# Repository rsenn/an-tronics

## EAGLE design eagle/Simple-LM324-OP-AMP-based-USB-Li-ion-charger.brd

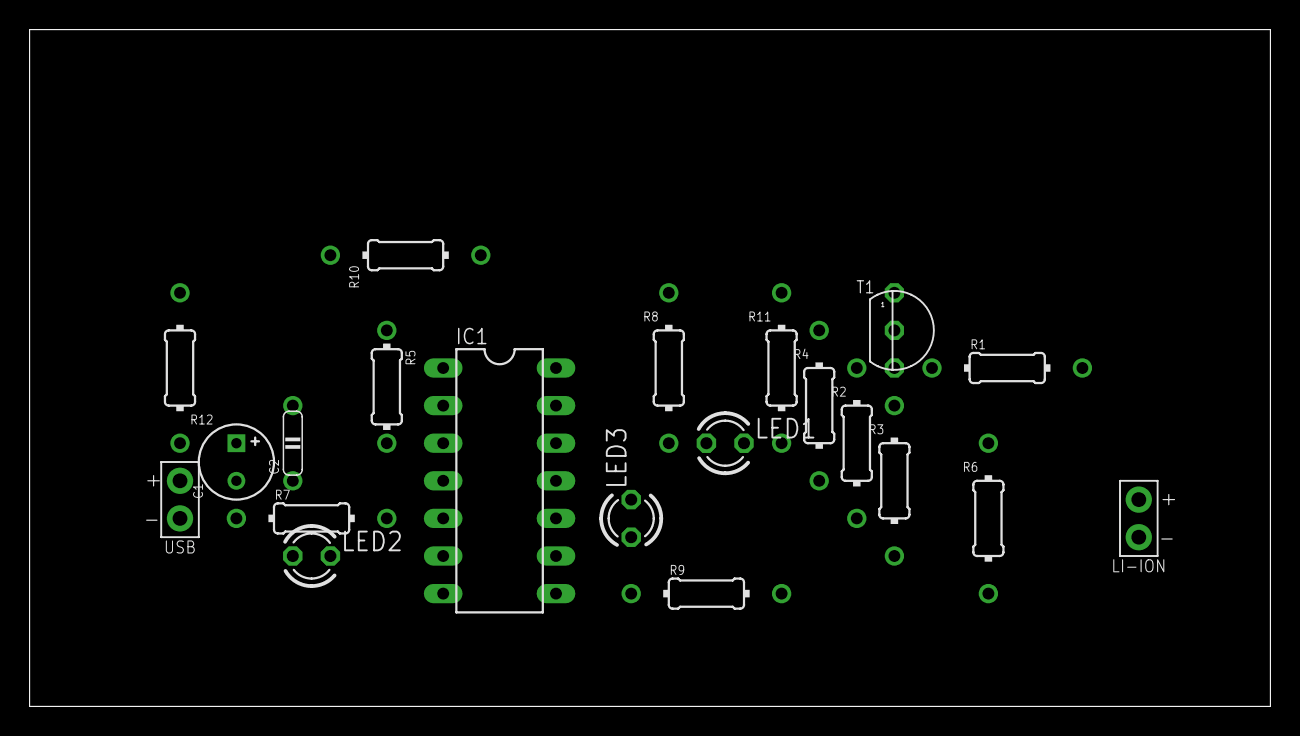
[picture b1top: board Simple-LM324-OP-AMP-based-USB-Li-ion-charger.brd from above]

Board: 2 copper layers, 83.8 x 45.7 mm, 21 parts (0 on the bottom side), 13 nets, no tracks yet.

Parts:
C1: 100uF/16V; E2,5-5
C2: 68nF; C050-020X044
IC1: LM324N; DIL14
LED1: Red; LED3MM
LED2: Green; LED3MM
LED3: Blue; LED3MM
LI-ION: SPAD+-+-; SPAD+-
R1: 1; 0204/10
R2: 2.7k; 0204/10-V
R3: 2.2k; 0204/10-V
R4: 220; 0204/10-V
R5: 470; 0204/7-V
R6: 4.7k; 0204/10-V
R7: 3.6k; 0204/10
R8: 680; 0204/10-V
R9: 1k; 0204/10
R10: 680k; 0204/10-V
R11: 470; 0204/10-V
R12: 12k; 0204/10-V
T1: BC327; TO92
USB: SPAD+--+; SPAD-+

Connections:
GND: C1.-, C2.1, IC1.11, LED2.A, LED3.K, LI-ION.1, R7.1, USB.1
unnamed: IC1.12, R5.1, R12.2
unnamed: IC1.14, R5.2, R8.1, R10.2
unnamed: C2.2, IC1.13, R10.1
unnamed: IC1.9, LED2.K, R3.2
unnamed: LED3.A, R9.1
unnamed: IC1.8, LED1.K, R9.2, R11.2
unnamed: LED1.A, R8.2
unnamed: R4.1, R11.1, T1.2
unnamed: R1.1, R2.2, R3.1, T1.1
unnamed: LI-ION.2, R1.2, R6.1
unnamed: IC1.10, R6.2, R7.2
V+: C1.+, IC1.4, R2.1, R4.2, R12.1, T1.3, USB.2

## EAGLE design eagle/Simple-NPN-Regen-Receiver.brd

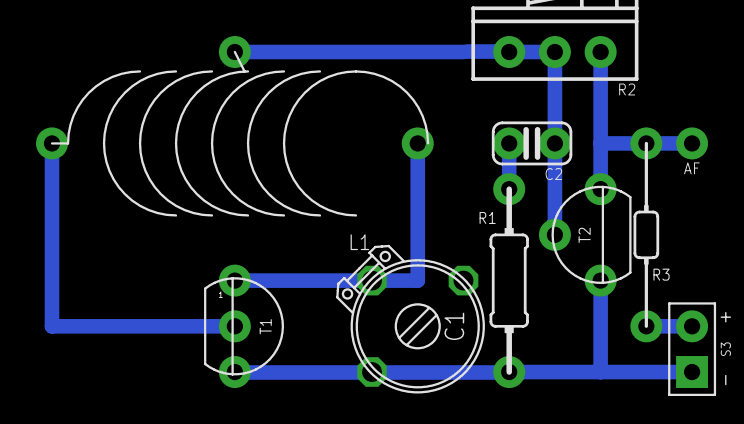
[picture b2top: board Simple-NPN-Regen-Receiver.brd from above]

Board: 2 copper layers, 10 parts (0 on the bottom side), 7 nets.

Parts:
AF: HPORT; SPAD
C1: 1 - 20pF; TRIM-2222-808
C2: 1nF; C025-024X044
L1: 0.2μH; L-08/20V-TAPM
R1: 47Ω; 0204/10-V
R2: 100kΩ; POT
R3: 10kΩ; 0202/10-V
S3: VCC_GNDR; SPAD+-
T1: 2N2222; TO92
T2: 2N3904; TO92-EBC-A

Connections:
GND: C1.3, R1.2, S3.1, T1.3, T2.E
unnamed: C2.2, R1.1
unnamed: L1.1, T1.2
unnamed: C2.1, L1.T, R2.E, R2.S, T2.B
unnamed: C1.2, L1.2, T1.1
unnamed: AF.1, R2.A, R3.2, T2.C
VCC: R3.1, S3.2

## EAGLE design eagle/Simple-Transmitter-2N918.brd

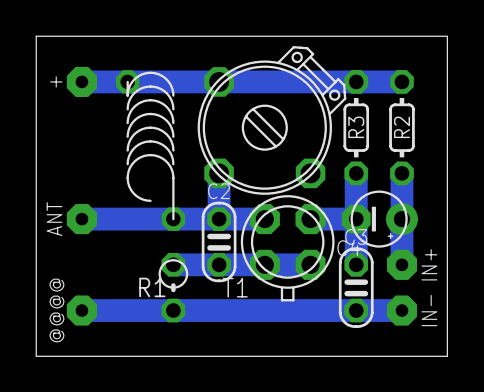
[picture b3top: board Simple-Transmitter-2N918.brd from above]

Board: 2 copper layers, 22.8 x 17.8 mm, 14 parts (0 on the bottom side), 6 nets.

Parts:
+: SPAD
@@@@: SPAD
ANT: ANT; SPAD
C1: 1.6 - 15pF; TRIM-2222-808
C2: 4.7pF; C025-020X036
C3: 1nF; C025-020X036
C4: 1μF; E2,5-3
IN+: SPAD
IN-: SPAD
L1: 1μH; L-04/7
R1: 2.2Ω; 0202V
R2: 22kΩ; 0202/5
R3: 47kΩ; 0202/5
T1: 2N918; TO-72

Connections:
+UB: +.1, C1.3, L1.1, R2.2, R3.2
GND: @@@@.1, C3.2, IN-.1, R1.1
IN+: C4.+, IN+.1, R2.1
unnamed: ANT.1, C1.2, C2.1, L1.2, T1.3
unnamed: C2.2, R1.2, T1.1, T1.4
unnamed: C3.1, C4.-, R3.1, T1.2

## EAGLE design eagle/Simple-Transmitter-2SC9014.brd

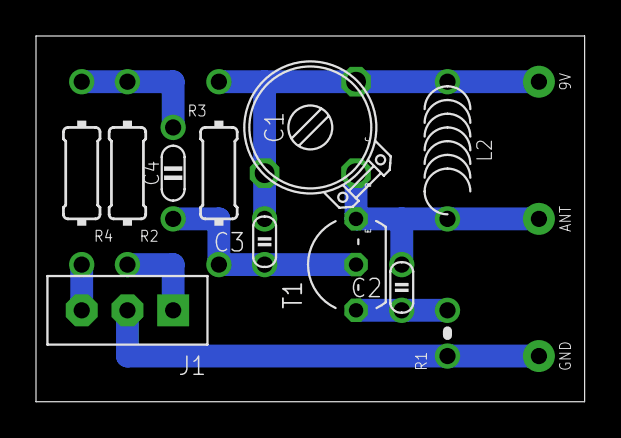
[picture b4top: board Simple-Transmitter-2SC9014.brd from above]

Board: 2 copper layers, 30.5 x 20.3 mm, 14 parts (0 on the bottom side), 8 nets.

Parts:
9V: SPAD
ANT: ANT; SPAD
C1: 1.6-15pF; TRIM-2222-808
C2: 4.7pF; C025-015X024
C3: 1nF; C025-015X024
C4: 10nF; C050-020X036/V
GND: SPAD
J1: CONN-3P-3P; CONN-3P
L2: 1μH; L-04/7
R1: 100Ω; 0204/2V
R2, R4: 47kΩ; 0204/10-V
R3: 10kΩ; 0204/10-V
T1: 2SC9014; TO92-EBC

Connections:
+UB: 9V.1, C1.3, C3.1, L2.2, R3.1
GND: GND.1, J1.2, R1.1
unnamed: J1.3, R4.1
unnamed: ANT.1, C1.2, C2.1, L2.1, T1.C
unnamed: C2.2, R1.2, T1.E
unnamed: J1.1, R2.1
unnamed: C3.2, C4.1, R3.2, T1.B
unnamed: C4.2, R2.2, R4.2

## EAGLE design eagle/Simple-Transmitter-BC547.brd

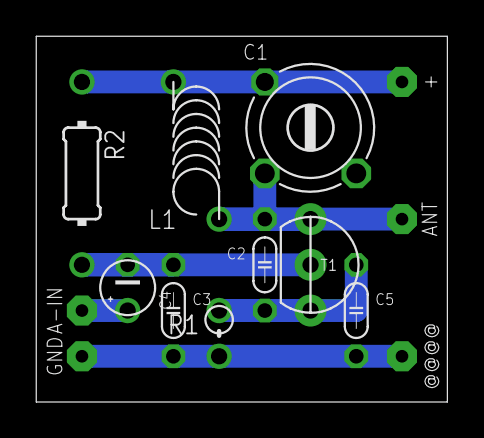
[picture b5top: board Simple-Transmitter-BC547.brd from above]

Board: 2 copper layers, 22.8 x 20.3 mm, 14 parts (0 on the bottom side), 6 nets.

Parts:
+: SPAD
@@@@: SPAD
A-IN: SPAD
ANT: ANT; SPAD
C1: 1.5-16pF; TRIM808-45
C2: 4.7pF; C050-020X036-M
C3, C5: 1nF; C050-020X036
C4: 1μF; E2,5-3
GND: SPAD
L1: 1μH; L-04/8V
R1: 100Ω; 0202V
R2: 10kΩ; 0204/10-V
T1: BC547; TO92-CBE

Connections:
AIN: A-IN.1, C4.+
GND: @@@@.1, C3.2, C5.2, GND.1, R1.1
unnamed: ANT.1, C1.2, C2.1, L1.1, T1.C
unnamed: C2.2, C5.1, R1.2, T1.E
unnamed: C3.1, C4.-, R2.1, T1.B
VCC: +.1, C1.3, L1.2, R2.2
